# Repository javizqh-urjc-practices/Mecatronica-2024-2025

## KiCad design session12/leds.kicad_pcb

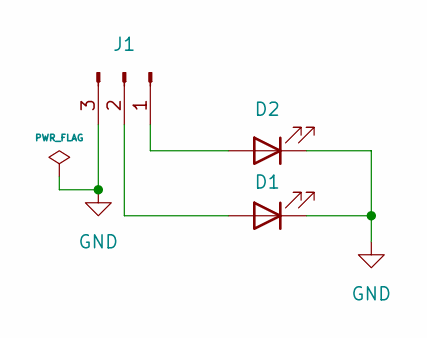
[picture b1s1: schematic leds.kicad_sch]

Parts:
D1, D2: LED; LED_D3.0mm
J1: Conn_01x03_Pin; PinHeader_1x03_P2.54mm_Vertical

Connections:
GND: D1.1 (K), D2.1 (K), J1.3
unnamed: D1.2 (A), J1.2
unnamed: D2.2 (A), J1.1

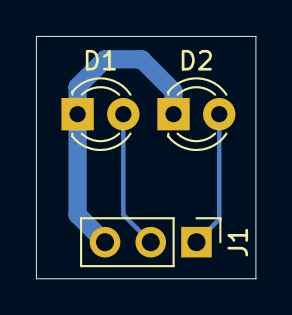
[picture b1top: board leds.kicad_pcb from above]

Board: 2 copper layers, 12.2 x 13.5 mm, 3 parts (0 on the bottom side), 3 nets.

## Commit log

2024-09-11 Create LICENSE
2024-09-11 Challenge 1
2024-09-11 Ch1 video
2024-09-11 Adding 1 image
2024-09-11 Adding img 2
2024-09-11 Adding ch2 video
2024-09-11 Moving files
2024-09-11 Add ch3
2024-09-11 Adding readme
2024-09-11 Add mp4 videos
2024-09-11 Update gifs
2024-09-11 Add .test.md
2024-09-16 Adding session2 part1
2024-09-16 Uploading Inkscape rect
2024-09-16 Update plain svg
2024-09-18 Adding session 3 challenges
2024-09-18 Adding ch3
2024-09-18 Add ch4
2024-09-18 Add ch5
2024-09-18 Update ch5
2024-09-18 Add ch6
2024-09-18 Add ch7
2024-09-18 Add ch8
2024-09-18 Add ch9
2024-09-18 Add ch10
2024-09-23 Add ch11
2024-09-23 White text
2024-09-23 Dark text
2024-09-23 Add ch12
2024-10-02 Update session4
2024-10-02 Update cutrebot
2024-10-02 Update session 5
2024-10-02 Adding ch5
2024-10-02 Add ch2
2024-10-07 Update session 6
2024-10-09 Update session 7
2024-10-16 Adding session8
2024-10-16 Add session 9
2024-10-21 Add session 10
2024-10-28 Update session 12
2024-11-04 Add some challenges
2024-11-04 Adding the rest of the challenges
2024-11-06 Add today
2024-11-11 Add session15
2024-11-13 Add new session
2024-11-18 Add img
2024-11-18 Add images 14
2024-11-18 Add img 13
2024-11-20 Add Ex
2024-11-20 Add stuff
2025-01-02 Add images
